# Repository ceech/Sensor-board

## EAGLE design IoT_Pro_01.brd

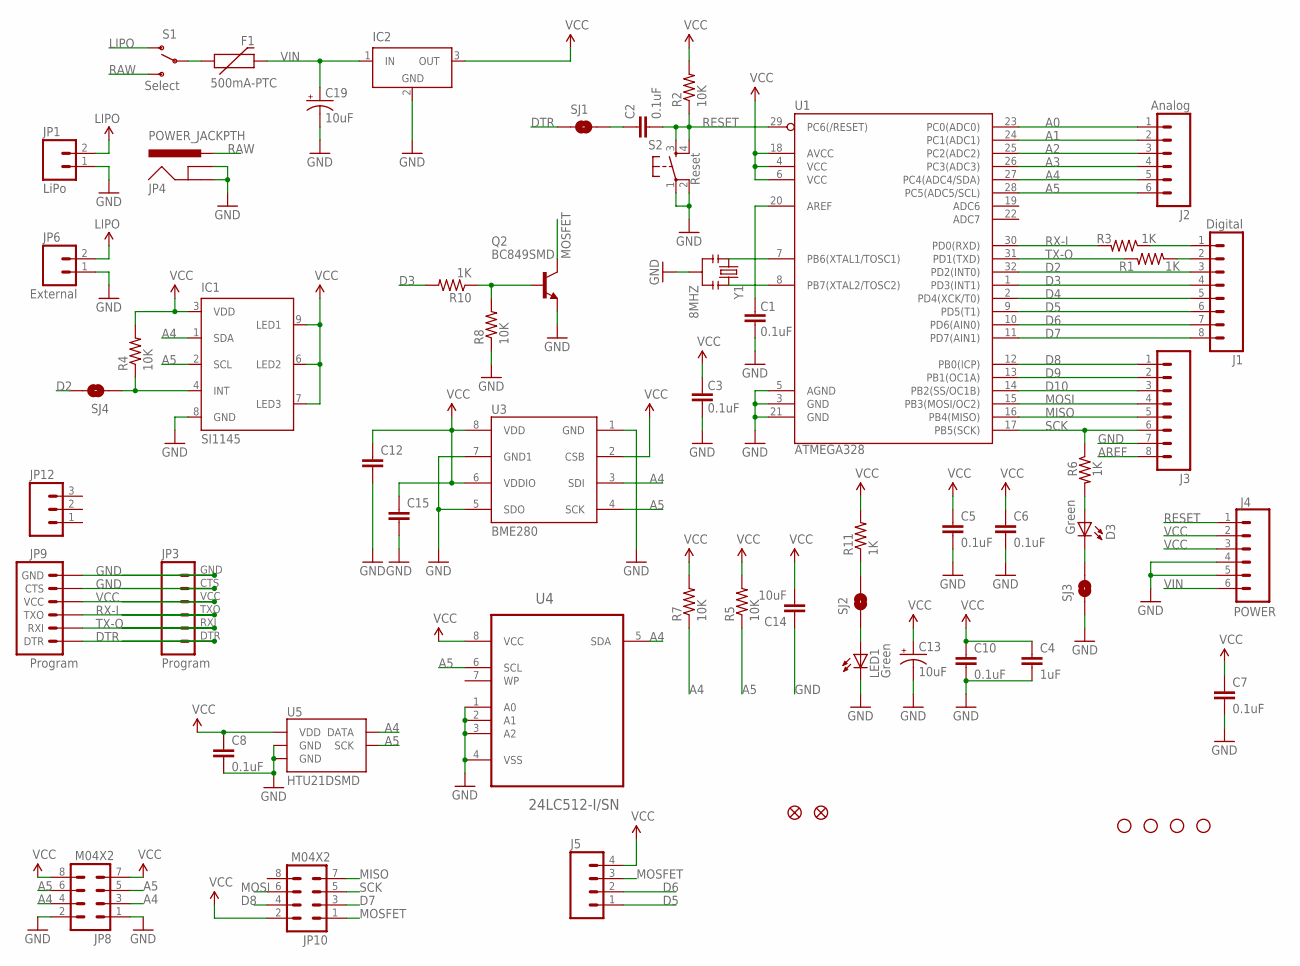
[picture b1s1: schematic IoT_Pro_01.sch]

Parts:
C1, C2, C3, C5, C6, C7, C8, C10: 0.1uF; 0805
C4: 1uF; 0805
C12, C15: CAP0805; 0805
C13, C19: 10uF; EIA3216
C14: 10uF; 0805
D3: Green; PLCC2
F1: 500mA-PTC; PTC-1206
IC1: SI1145; QFN-10
IC2: LT1129CST5; SOT223
J1: Digital; 1X08
J2: Analog; 1X06
J3: M081X08; 1X08
J4: POWER; 1X06
J5: M04PTH; 1X04
JP1: LiPo; MOLEX-1X2
JP2, JP5: FIDUCIAL1X2.5; FIDUCIAL-1X2.5
JP3: Program; 1X06
JP4: POWER_JACKPTH; POWER_JACK_PTH
JP6: External; 1X02
JP8, JP10: M04X2; 2X4
JP9: Program; 1X06-SMD
JP12: M03PTH; 1X03
LED1: Green; PLCC2
Q2: BC849SMD; SOT23-BEC
R1, R3, R6, R10, R11: 1K; 0805
R2, R4, R5, R7, R8: 10K; 0805
S1: Select; SWITCH-SPST-SMD-A
S2: Reset; TACTILE_SWITCH_SMD
SJ1, SJ2, SJ3, SJ4: SOLDERJUMPERNC2; SJ_2S-NOTRACE
U1: ATMEGA328; TQFP32-08
U3: BME280
U4: 24LC512-I/SN; SOIC127P600X175-8N
U5: HTU21DSMD; HTU21D
U$1, U$3, U$9, U$10: STAND-OFFTIGHT; STAND-OFF-TIGHT
Y1: 8MHZ; RESONATOR-SMD

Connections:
A0: J2.1, U1.23 (PC0(ADC0))
A1: J2.2, U1.24 (PC1(ADC1))
A2: J2.3, U1.25 (PC2(ADC2))
A3: J2.4, U1.26 (PC3(ADC3))
A4: IC1.1 (SDA), J2.5, JP8.3, JP8.4, R7.1, U1.27 (PC4(ADC4/SDA)), U3.3 (SDI), U4.5 (SDA), U5.DATA
A5: IC1.2 (SCL), J2.6, JP8.5, JP8.6, R5.1, U1.28 (PC5(ADC5/SCL)), U3.4 (SCK), U4.6 (SCL), U5.SCK
AREF: C1.2, J3.8, U1.20 (AREF)
D2: J1.3, SJ4.2, U1.32 (PD2(INT0))
D3: J1.4, R10.2, U1.1 (PD3(INT1))
D4: J1.5, U1.2 (PD4(XCK/T0))
D5: J1.6, J5.1, U1.9 (PD5(T1))
D6: J1.7, J5.2, U1.10 (PD6(AIN0))
D7: J1.8, JP10.3, U1.11 (PD7(AIN1))
D8: J3.1, JP10.4, U1.12 (PB0(ICP))
D9: J3.2, U1.13 (PB1(OC1A))
D10: J3.3, U1.14 (PB2(SS/OC1B))
DTR: JP3.DTR (1), JP9.1 (DTR), SJ1.1
GND: C1.1, C3.1, C4.2, C5.2, C6.2, C7.2, C8.2, C10.2, C12.2, C13.C (-), C14.1, C15.2, C19.C (-), IC1.8 (GND), IC2.2 (GND), IC2.4 (GND), J3.7, J4.4, J4.5, JP1.1, JP3.CTS (5), JP3.GND (6), JP4.GND, JP4.GNDBREAK, JP6.1, JP8.1, JP8.2, JP9.5 (CTS), JP9.6 (GND), LED1.C, Q2.E, R8.1, S2.1, S2.2, SJ3.1, U1.3 (GND), U1.5 (AGND), U1.21 (GND), U3.1 (GND), U3.5 (SDO), U3.7 (GND1), U4.1 (A0), U4.2 (A1), U4.3 (A2), U4.4 (VSS), U5.7 (GND), U5.GND, Y1.2
LIPO: JP1.2, JP6.2, S1.1 (O)
MISO: J3.5, JP10.7, U1.16 (PB4(MISO))
MOSFET: J5.3, JP10.1, Q2.C
MOSI: J3.4, JP10.6, U1.15 (PB3(MOSI/OC2))
unnamed: C2.1, SJ1.2
unnamed: U1.7 (PB6(XTAL1/TOSC1)), Y1.1
unnamed: U1.8 (PB7(XTAL2/TOSC2)), Y1.3
unnamed: LED1.A, SJ2.1
unnamed: D3.A, R6.2
unnamed: R11.1, SJ2.2
unnamed: D3.C, SJ3.2
unnamed: IC1.4 (INT), R4.1, SJ4.1
unnamed: Q2.B, R8.2, R10.1
unnamed: F1.1, S1.2
RAW: JP4.PWR, S1.3 (S)
RESET: C2.2, J4.1, R2.1, S2.3, S2.4, U1.29 (PC6(/RESET))
RX-I: JP3.TXO (3), JP9.3 (TXO), R3.2, U1.30 (PD0(RXD))
RX-IP: J1.2, R1.1
SCK: J3.6, JP10.5, R6.1, U1.17 (PB5(SCK))
TX-O: JP3.RXI (2), JP9.2 (RXI), R1.2, U1.31 (PD1(TXD))
TX-OP: J1.1, R3.1
VCC: C3.2, C4.1, C5.1, C6.1, C7.1, C8.1, C10.1, C12.1, C13.A (+), C14.2, C15.1, IC1.3 (VDD), IC1.6 (LED2), IC1.7 (LED3), IC1.9 (LED1), IC2.3 (OUT), J4.2, J4.3, J5.4, JP3.VCC (4), JP8.7, JP8.8, JP9.4 (VCC), JP10.2, R2.2, R4.2, R5.2, R7.2, R11.2, U1.4 (VCC), U1.6 (VCC), U1.18 (AVCC), U3.2 (CSB), U3.6 (VDDIO), U3.8 (VDD), U4.8 (VCC), U5.VDD
VIN: C19.A (+), F1.2, IC2.1 (IN), J4.6

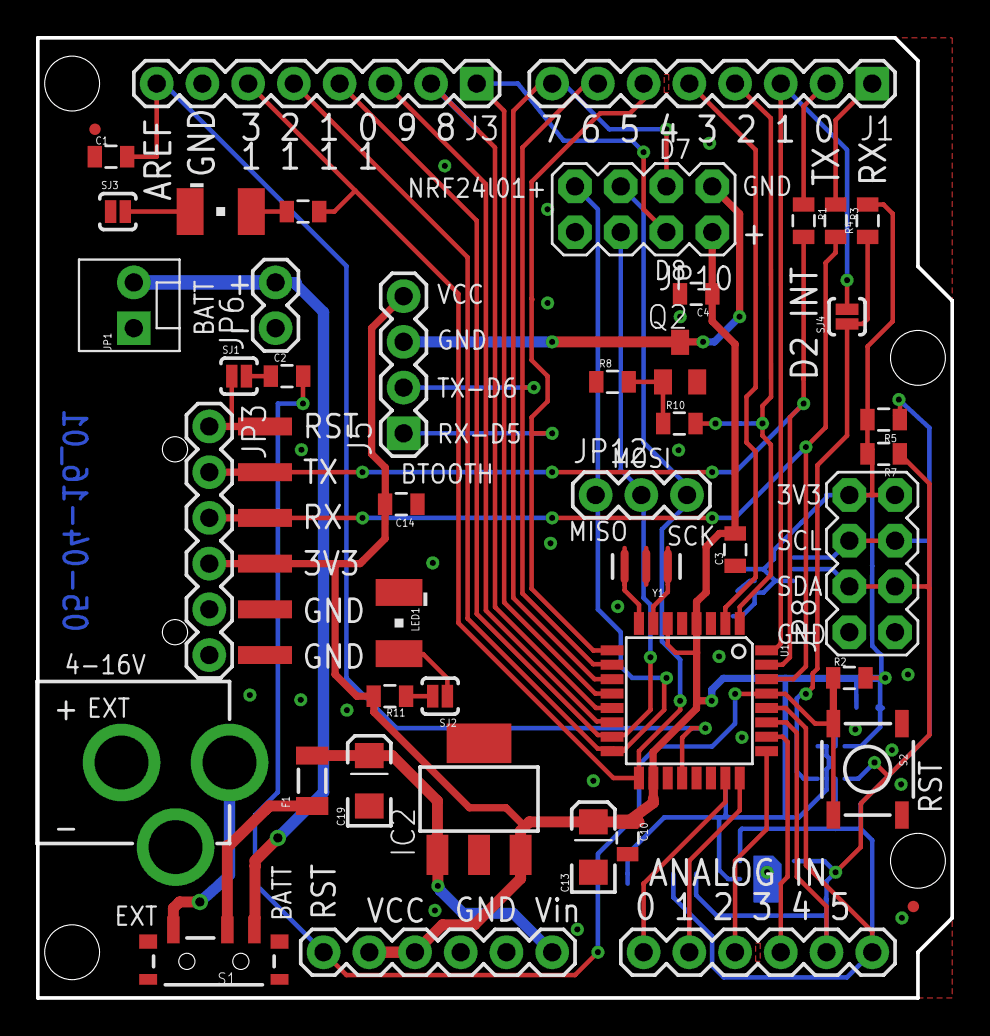
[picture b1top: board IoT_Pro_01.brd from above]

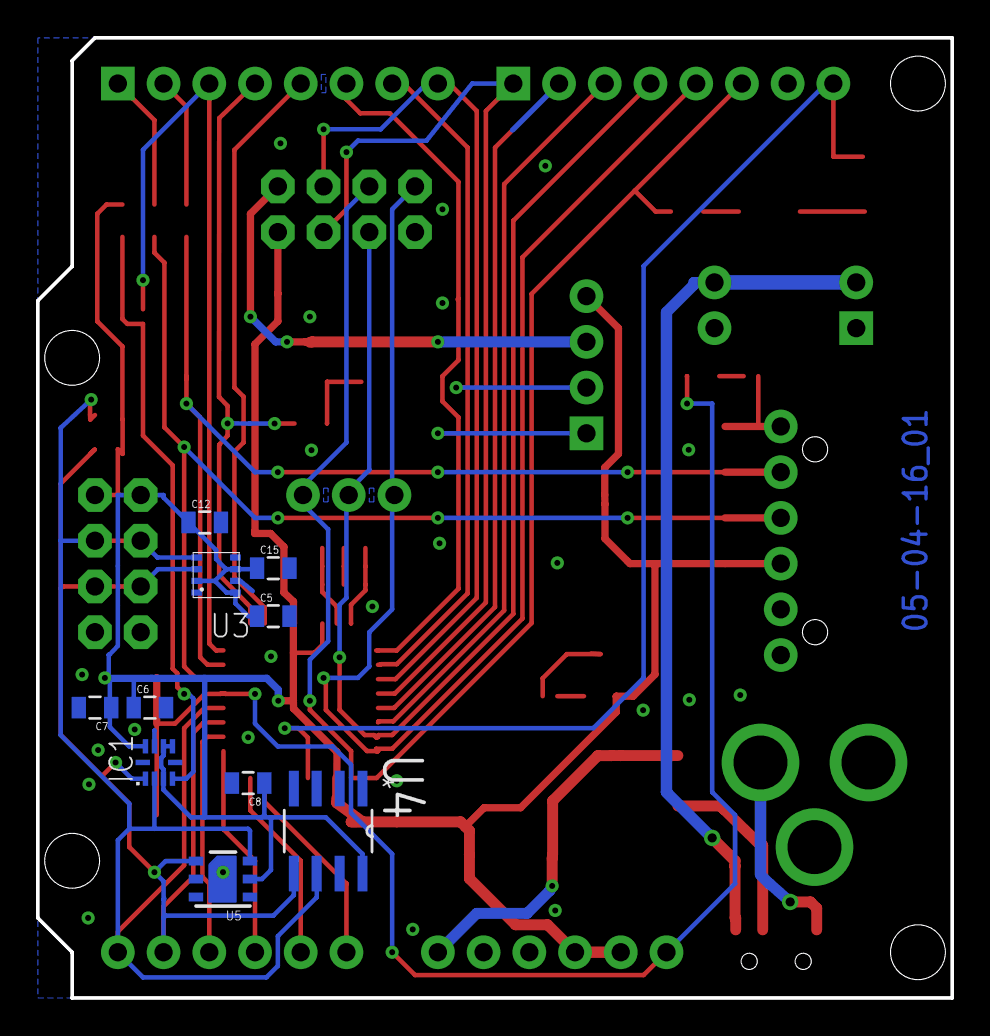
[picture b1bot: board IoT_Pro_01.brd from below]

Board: 2 copper layers, 50.8 x 53.3 mm, 60 parts (10 on the bottom side), 41 nets.

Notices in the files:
parts and their libraries:
SparkFun-Connectors: Licensing: Creative Commons ShareAlike 4.0 International - https://creativecommons.org/licenses/by-sa/4.0
